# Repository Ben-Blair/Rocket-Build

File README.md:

# RocketSenior — canard-guided high power rocket

Senior capstone project: demonstrate closed-loop lateral guidance of a high power rocket
using forward canards, and handle the canard-wake-on-aft-fin interference problem
correctly.

This repository currently holds the **preliminary sizing tool**. It exists to answer the
questions you have to answer *before* you can draw anything in OpenRocket: how big is the
tube, how big are the fins, which motor, and can the canards actually do anything.

## Why a sizing tool instead of just using OpenRocket

OpenRocket is a verification tool. It answers "is *this specific* rocket stable, and how
high does it go." It cannot answer "what should my rocket be," because that depends on
constraints it knows nothing about:

- the internal diameter needed to house four canard servos (this sets your airframe size),
- the lateral acceleration you need for a visible manoeuvre,
- the static margin you are willing to trade away to get control authority,
- whether the canard wake reverses the sign of your roll moment.

This tool computes those, converges on a baseline, and then prints the numbers to type
into OpenRocket for an independent cross-check. Use both. Disagreement between them is
information.

## Quick start

```bash
pip install -r requirements.txt

python scripts/packaging_report.py   # what diameter do the actuators force on you?
python scripts/fetch_motors.py --diameter 54 --classes J K   # real thrust curves
python scripts/motor_trade.py        # rank every real L2 motor against the airframe
python scripts/sweep.py              # which (tube, motor, fin) combos meet requirements?
python scripts/baseline.py --plot    # full analysis + OpenRocket entry values
```

## Layout

```
out/
  RocketSenior.ork   GENERATED by scripts/make_ork.py -- do not hand-edit, see below
```

### The .ork is a build artifact, not the design

`out/RocketSenior.ork` is written from the same `DesignParams` the Python tool uses, and
`scripts/openrocket_check.py` regenerates it on every run. That is the point: the two
models cannot drift apart.

It also means **anything you change in the OpenRocket GUI and save back to that path is
destroyed the next time you run the check.** Open it to look, simulate, and cross-check
freely. If you want to tinker, `Save As` somewhere outside `out/` first. If a change is
worth keeping, it belongs in `design/configure.py` or `scripts/make_ork.py`, so that the
next regeneration carries it forward.

```
design/
  atmosphere.py   US Standard Atmosphere 1976, troposphere
  aero.py         Barrowman CNa & CP buildup, component drag buildup
  avionics.py     nav bay / nose packing, and the D7 flight computer trade
  bay.py          the printed canard bay: servo pockets, bearing seats, retainers
  configure.py    parameter set -> full vehicle -> requirement scoring, and the
                  frozen baseline airframe every script imports
  control.py      canard pitch authority, roll authority, wake interference, crossrange
  estimation.py   D8: observability per flight phase, attitude error budget, sensor specs
  flight_computer.py  the Stage 2 board: BOM, power budget, log budget, board envelope
  flutter.py      fin flutter margin
  geometry.py     nose / tube / fin set definitions, Barrowman CP geometry
  hinge.py        the hinge as a load path: shaft, bearing, coupling, root joint
  joints.py       all four tube joints -- a coupler costs bore, not length
  mass.py         geometric structural mass + editable subsystem budget, CG
  materials.py    material allowables, in one place
  motors.py       RASP .eng thrust curve parser + placeholder generic motors
  onshape.py      minimal Onshape REST API client
  onshape_build.py  emits Onshape Part Studio feature JSON
  packaging.py    actuator bay packaging + hinge moment + servo torque margin
  recovery.py     dual-deploy sizing, descent time, wind drift, soft-goods packing
  seal.py         the aft gas seal and the internal bulkhead, sized as pistons
  horizontal.py   horizontal-launch 3-DOF: fly the manoeuvre, then score the turn
  trajectory.py   3-DOF RK4 ascent to apogee
  tube_section.py airframe survival where holes are cut through it
  venting.py      static ports and bay vents: which volumes the altimeter may sense
scripts/
  agility_sweep.py      how agile can this airframe legally be, and what stops it
  avionics_report.py    nav bay + nose packing report and verdict
  avionics_trade.py     D7: the three flight computer architectures
  baseline.py           detailed baseline report + OpenRocket values
  bay_report.py         printed canard bay geometry and margins
  burn_time_study.py    why burn time is not a control-time knob
  canard_sweep.py       drives the CAD canards through +/-8 deg, checks clearances
  estimation_trade.py   D8: the four sensor sets, and what the estimate can know
  fetch_motors.py       download real .eng thrust curves from ThrustCurve.org
  hinge_report.py       hinge stack loads, fits and buildability
  horizontal_agility_sweep.py  the same search flown FLAT, where the answer changes
  make_*.py             build geometry in Onshape from the design modules
  motor_trade.py        rank every available L2 motor against the baseline airframe
  openrocket_check.py   automated cross-check against OpenRocket's engine
  packaging_report.py   diameter vs servo class table
  place_*.py            place built parts into Onshape Assembly 1
  recovery_study.py     descent, drift and the recovery footprint constraint
  robustness.py         Monte Carlo on static margin; sets the aft fin size
  flight_computer_report.py  the Stage 2 board's BOM, power, logging and envelope
  seal_report.py        the aft gas seal argument and check
  sil_demo.py           software-in-the-loop: closed-loop roll hold, bank-to-turn,
                        R12 failsafe -- synthetic sensors, no hardware
  sweep.py              design space sweep against requirements
  verify_cad.py         cross-check the design numbers against the Onshape model
  virtual_flight.py     3-D virtual flight: ballistic, skid-to-turn, bank-to-turn
docs/
  00-requirements.md    requirements, constraints, scoping, regulatory actions
  01-next-steps.md      ordered plan, the state of play, and 36 corrections
  02-motor-selection.md L2 motor trade study and decision
  03-openrocket-correlation.md  automated cross-check against OpenRocket's engine
  04-bill-of-materials.md       frozen parts list, masses and costs
  05-canard-module-build.md     CAD build sheet for the canard module
  06-avionics-selection.md      D7: the flight computer, and why it is staged
  07-state-estimation.md        D8: what the flight computer can know, and when
  11-agility-comparison.md      what this vehicle lacks versus a canard missile (VERTICAL)
  12-horizontal-agility.md      the same question flown flat -- 8.97 deg/s, and the
                                hinge bearing is what stops it. PROPOSAL, not frozen
  13-sil-demo.md                software-in-the-loop closed loop: how to run it, what
                                it proves, what it does not
  14-flight-computer-bom.md     the Stage 2 board, part by part: what to order, the
                                power and log budgets, and what was rejected
```

## How this fits with OpenRocket and RocketPy

Three tools, each for what it is actually good at. Do not try to make one do everything.

| Tool | Use it for | Do not use it for |
|---|---|---|
| **This repo** | Actuator packaging, control derivatives (`Cm_delta`, `Cl_delta`, `Cl_p`), canard/aft-fin wake interference, hinge moments, requirement-driven sizing sweeps across 100+ motors | Final apogee or drag numbers |
| **OpenRocket** | Validated stability and trajectory, Mach-dependent drag, dual-deploy and recovery sizing, fin flutter, the airframe truth a reviewer will trust | Anything involving a deflected control surface. It has no concept of one |
| **RocketPy** | 6-DOF flight with wind, Monte Carlo dispersion, and closed-loop control. `LinearGenericSurface` takes coefficient derivatives as functions of Mach, alpha, beta and body rates; `Controller` runs your control law at a fixed sampling rate against simulated IMU and barometer sensors | Preliminary sizing; it needs a vehicle before it can fly one |

The intended pipeline: size here → validate the passive airframe in OpenRocket → export
the derivatives from here into a RocketPy `LinearGenericSurface` → close the loop in 6-DOF
→ fly, and replace the interference factors with measured values.

## Model validity and what you must not trust

Read this before you quote any number from this tool in a report.

| Component | Status | Notes |
|---|---|---|
| Atmosphere | Solid | Standard model, valid to 11 km. |
| Barrowman CNa / CP | Good | Standard method. Valid subsonic, small alpha, attached flow. |
| Body lift (Galejs) | Approximate | Nonlinear term linearised about 4 deg alpha. |
| Drag buildup | ±20% at best | Component buildup with empirical form factors. Cross-check against OpenRocket, then against measured flight data. |
| Mass budget | Estimate | Every subsystem line is a guess until you weigh the part. Weigh things. |
| Trajectory | Good given the above | 3-DOF, no wind, perfect weathercocking. |
| Inertias | ±30% bulk, canard module measured | Crude analytical estimate for the airframe, with the canard module's CAD tensor superposed (`control.MEASURED_COMPONENTS`). Measure the rest before tuning gains. |
| Canard control derivatives | Approximate | Linear, quasi-steady, no wake effect on the canards themselves. |
| **Canard/aft-fin interference** | **Weakest part** | Empirical factors with no validation. Trends are believable, absolute values are not. Must be measured in flight. |
| Motor data | Real | 102 available 54 mm J/K certification curves from ThrustCurve.org in `data/motors/`. The `GENERIC` motors in `motors.py` are invented placeholders, kept only so the tool runs before a download. |

The interference model is the one to be honest about in your defense: it is a
physically-motivated parameterisation, not a validated prediction. The project plan
therefore makes measuring it a flight test objective rather than an assumption.

## Baseline result

75 mm (3 in) fiberglass airframe, 79.4 mm OD, 1361 mm long, 4 canards interdigitated 45°
from 4 aft fins, on a Cesaroni Pro54 J449 Blue Streak, actuated by four KST X08 Plus V6.0
servos on direct drive, with 100 g of nose ballast. 6.10 kg wet / 5.48 kg dry, apogee
1379 m (4525 ft), max Mach 0.531, static margin 2.03 cal at rail exit rising to 2.52 in
coast, 1.96 g of lateral authority at 8° of canard deflection, giving 424 m of crossrange
over an 11.4 second usable control window. Recovery is an 18 in drogue and 56 in main
deployed at 200 m, landing at 5.0 m/s after a ~0.93 km walk in a 15 mph wind.

Both fin sets were sized *together* by a Monte Carlo on margin robustness rather than
independently by nominal stability — canard semispan 0.85 cal, aft semispan 1.55 cal. They
pull in opposite directions, and searching them jointly under a probabilistic margin
constraint beats trading one against the other. See `docs/00-requirements.md` §7.

**The nose ballast is part of the design, not a contingency.** Real 9 g servos in place of
the 55 g budget placeholder removed ~180 g from ahead of the CG, which took P(SM < 1.0) to
1.8% against R1's 1% limit. 75 g of ballast is the minimum that satisfies R1; 100 g is the
design point and brings it to 0.6%. It is deliberately the last free parameter — a washer
stack you set after weighing the built vehicle, rather than fin area you commit to when you
cut the tube. See §7.1.

Every number above is an output of `scripts/baseline.py`. Regenerate them rather than
editing them by hand; they will move as the mass budget is replaced with weighed parts.

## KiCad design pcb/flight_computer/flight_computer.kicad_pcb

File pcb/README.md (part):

# `pcb/` — the Stage 2 flight computer board

One project so far: **`flight_computer/`**, the custom STM32F405 board that
`docs/06` selected, `docs/07` gave sensors to, and `docs/14` turned into a BOM. This
directory is where that BOM becomes a schematic and a board. **As of 2026-09-24 it is
placed, routed, DRC-clean and has a JLCPCB fab + assembly package** in
`flight_computer/fab/` — read `fab/ORDERING.md` and "What is not done" at the bottom before
you order: two parts are out of stock and every assembly rotation needs a look in JLC's
preview.

## Opening it

```
open pcb/flight_computer/flight_computer.kicad_pro
```

The schematics are still **KiCad 8 file format** (`.kicad_sch` 20231120) and open
unchanged in KiCad 8, 9 and 10. **`flight_computer.kicad_pcb` no longer is** — the
layout pass (below) is done with KiCad's own `pcbnew` Python module, which saves in
whatever format the KiCad it's running under uses, and on this machine that's
**KiCad 10.0.6, board format 20260206**. Opening the `.kicad_pcb` in KiCad 8 or 9 will
prompt to upgrade the file. If that matters, say so before more layout work happens
on it — reverting is easy now and gets harder every pass after.

The symbol and footprint bodies embedded in the files were copied from this
machine's libraries — so if a symbol looks odd in another KiCad install, that is the
first place to look.

`sym-lib-table` registers one project-local symbol library,
`RocketSenior.kicad_sym`, for the three parts that needed one (below).
`fp-lib-table` registers one project-local **footprint** library,
`RocketSenior.pretty`, holding exactly one footprint —
`MMC5983MA_LGA-16_3x3mm_P0.5mm`, redrawn for `U5`, for the reason in "MMC5983MA"
below. Both tables use `${KIPRJMOD}`, so there is nothing to install; everything
else is stock KiCad libraries.

### Verified state

Reproducible from a clean checkout by regenerating in order (see "How the board gets
built" below — running only some of these steps, or out of order, does not match this
table):

| check | result |
|---|---|
| `kicad-cli sch erc` | **0 errors, 0 warnings** |
| `kicad-cli pcb drc --severity-all` | **0 errors, 0 unconnected**; 14 warnings, all library-footprint cosmetics — listed under "Routing" |
| netlist vs. `scaffold/design.py` | **57 real nets, exact match** (96 in the raw KiCad netlist — the other 39 are its own one-per-pin `unconnected-(REF-Pad)` placeholders for every NC pin, not a discrepancy) |
| footprint assigned on every component | **76 / 76** |
| `python scripts/pcb_placement_report.py` | **1 failure** (`C3`, accepted), median 2.60 mm |

```
bash pcb/flight_computer/scaffold/regen.sh      # close KiCad first; it refuses otherwise
```

which is, in order: ERC, netlist export, `gen_pcb.py`, `layout.py`, `finish.py` (hand-drawn
critical copper + Freerouting + silkscreen), full-severity DRC, the placement report, and
`fab.py`. Freerouting is **not deterministic** — to rebuild *this* board rather than an
equally valid re-route, pass `--ses routing/board.ses` to `finish.py` (see its docstring).
It needs `tools/freerouting-2.4.1.jar` (64 MB, gitignored): download it from
<https://github.com/freerouting/freerouting/releases>. Java is already installed.

`kicad-cli` is not on `PATH` by default on this machine; it lives at
`/Applications/KiCad/KiCad.app/Contents/MacOS/kicad-cli`.

**Do not run `layout.py` twice in a row on the same file, and do not run it without
regenerating the skeleton first.** It loads whatever `flight_computer.kicad_pcb`
already contains and adds a full new set of passives/vias/zones on top; run on its
own prior output it silently doubles everything and every number above stops
matching. `gen_pcb.py` always rebuilds the board from scratch, so the correct order
is always: export the netlist, run `gen_pcb.py`, then run `layout.py` exactly once.

Before 2026-09-24 the 133 unconnected items were every signal net — the board was placed
and planed but not routed. They are all routed now; see "Routing".

Nothing here moved by exclusion — every DRC violation was fixed in geometry:

| | first pass | then | now | why |
|---|---|---|---|---|
| DRC violations | 23 | 11 | **0** | 12 were `U5`'s adjacent-pad clearance (fixed in copper, see "MMC5983MA"); the last 11 were GND stitching vias landing on `U2`'s pads — see "Planes" below |
| unconnected items | 136 | 133 | **133** | the 3 unstitched `GND` pads are stitched; the rest is unrouted signal |
| placement failures | — | 14 | **2** | the pre-routing placement pass — see "Placement" below |

## Placement — the pass before routing, and the check that holds it

**ERC and DRC are connectivity checks and cannot see geometry.** Both passed on a board
whose 12 pF crystal load cap sat **21.5 mm** from its crystal, with the 8 MHz oscillator
node routed the length of the MCU and past the IMU. `design/pcb_placement.py` is the check
that closes that gap, `scripts/pcb_placement_report.py` prints it, and `scripts/baseline.py`
carries the verdict so it cannot regress quietly. Read that module's docstring before
changing a limit — in particular, why the check is scoped to two-terminal passives plus
three named nets rather than run over every pad.

What moved, and the measured effect:

| | before | now |
|---|---|---|
| `OSC_IN` (crystal to MCU, worst pad) | 14.39 mm | **3.75 mm** |
| `OSC_OUT` | 5.98 mm | **4.96 mm** |
| `GNSS_RF` (`U8` pin 11 to the u.FL) | 13.93 mm | **2.59 mm** |
| `C2`, 100 µF bulk, to the star point | 11.21 mm | **4.60 mm** |
| `R1`/`C4`, the regulator's enable and bypass | 14.3 / 13.6 mm | **2.99 / 1.98 mm** |
| median over all checked pads | 3.47 mm | **2.59 mm** |
| failures | 14 | **2** |

The moves that made room, all in `scaffold/gen_pcb.py`'s `PLACE`:

- **`J10` and `SW1` were in the two best pockets on the board** and are bring-up-only
  parts. `J10` (debug UART) held a 3.5 × 11.2 mm channel beside `U1` — which is *why*
  `C2`/`C4`/`R1` had been hand-relocated 14 mm away in an earlier pass, with a note saying
  the corner was saturated. It was saturated by a debug header. `SW1` sat in the only pocket
  that could take the crystal. Both are grouped with `J3` on the aft edge now; `NRST` is on
  the SWD header anyway, so `SW1` belongs there electrically as well as ergonomically.
- **`TP3` (a GND probe point) had claimed the gap between `U1` and its VIN cluster.** A test
  point's courtyard is 1.25 × 0.00 mm, so it slips into gaps no real part can claim.
- **`J5` moved to the forward edge** beside `U8`'s RF pad, which points at the nose where
  the antenna is. `U8` shifted 2.0 mm aft to open the strip — its courtyard is 11.8 mm wide
  against a 9.7 × 10.1 mm package and left only 3.0 mm of edge for a 4.4 mm connector.
- **`Y1` moved against `U2` pins 5/6, at 180°** so its `OSC_IN` pad faces the MCU and the two
  traces do not cross.

**`U5` did not move, and is confirmed not to have moved**: pad 1 is still at
(162.7500, 109.2250) — `pcb_placement.self_check()` asserts it on every run, because a
pad-rotation sign error would otherwise be invisible in the aggregate.

### The two remaining failures, both accepted

`C3.1` at **3.40 mm** and `R1.1` at **2.99 mm** against a 2.5 mm `VIN` limit. The aft-left
corner really is saturated once the four servo headers, the pack connector, the regulator,
the inductor and the power LED are in it — that part of the earlier note was right. Both are
about 1 mm over a limit set by judgement rather than by a datasheet. If the buck's input loop
ever needs to be tighter than this, the lever is `docs/14`'s own rule — *"if layout wants
more, take it out of height, not width"* — not another shuffle of the same corner.

## How the schematic is drawn, and why it looks like that

Four hierarchical sheets — `power`, `mcu`, `sensors`, `io` — under a root sheet that
carries the board-level notes.

**There are no drawn buses.** Every pin gets a short stub with a global label or a
power symbol on the end. That is a deliberate trade: it makes the netlist exactly
what `design.py` says and nothing else, and it means the auto-placement of symbols on
the sheet carries no meaning at all. **Rearranging the sheets into something a human
would draw is expected work, and it cannot break connectivity** as long as you move
labels with their pins. Sheet sizes were picked as the smallest ISO size each fit on
(io A3, power/sensors A2, mcu A1).

## Bus map — this is `docs/14`, unchanged

```
SPI1  CS1_IMU     PA4    ICM-42688-P    alone on the bus, 1 kHz burst on DMA
SPI2  CS2_MAG     PB12   MMC5983MA      100 Hz
      CS3_BARO    PC7    MS5611         50 Hz
SPI3  CS4_FLASH   PB5    W25Q128JV      log flash, write-mostly
USART1 PA9/PA10          MAX-M10S       10 Hz UBX
USART2 PA2/PA3           debug console  bring-up only
TIM4  CH1-4  PB6 PB7 PB8 PB9            4x servo PWM, 333 Hz / 1520 us
SWD   PA13 PA14 (+ PB3 SWO)
USB   PA11/PA12 full speed, 8 MHz HSE crystal
```

CS net names are `CS1_IMU`, `CS2_MAG`, `CS3_BARO`, `CS4_FLASH` so both `docs/14`'s
number and the function are in the name.

**Flash only — no microSD**, per `docs/14`'s socket-eject argument. The SDIO pins
(PC8-PC12/PD2) are not all free because SPI3 took PC10-PC12; if a microSD is ever
wanted, that is the trade to reopen.

**No pyro, no continuity, no e-match anything.** An independent StratoLoggerCF fires
the charges. This is `docs/14`'s non-negotiable and the board honours it.

## Things found while drawing it

These came out of reading datasheets to place pins, and several of them change a part,
a component count or a footprint. **None of them touches ±4000 or the airframe
freeze.**

### 1. `docs/14` names the wrong regulator — TPS62163 is 5.0 V, not 3.3 V

`docs/14`'s BOM row reads `3.3 V regulator | TPS62163DSGT`. TI's own device-options
table (SLVSAM2E, *TPS62160/61/62/63*, §5 Device Voltage Options) maps the suffixes:

| output | part |
|---|---|
| adjustable | TPS62160 |
| 1.8 V | TPS62161 |
| **3.3 V** | **TPS62162** |
| 5.0 V | TPS62163 |

**The 3.3 V part is TPS62162DSGT.** Verified against TI's own PDF, not a mirror:
`ti.com/lit/ds/symlink/tps62162.pdf`, SLVSAM2E §5 *Device Voltage Options*, which also
confirms DSG = WSON(8) and the DSG pinout the power sheet is wired to (1 PGND, 2 VIN,
3 EN, 4 FB, 5 AGND, 6 VOS, 7 SW, 8 PG).

**This is now fixed in all three places** — the schematic already had it, and
`docs/14-flight-computer-bom.md` and `design/flight_computer.py` have been changed from
`TPS62163DSGT` to `TPS62162DSGT`. `out/flight_computer.txt` was regenerated
(`python scripts/flight_computer_report.py --write`) so the report no longer copies the
wrong line. The intent in `docs/14` was never ambiguous ("3.3 V regulator", 2S in,
112 mA logic rail) — it was a wrong MPN, and ordering the line as written would have put
5.0 V onto the 3.3 V logic rail.

Wired per the same datasheet: `FB` (pin 5) to AGND, which is what TI specifies for
the fixed-output versions; `VOS` (pin 6) is the output sense and goes to the 3.3 V
rail; `PG` is open-drain and gets a 100 k pull-up, landed on PC13 so firmware can see
the rail come up.

### 2. The magnetometer needs a 10 µF capacitor that was in nobody's parts count

MMC5983MA **pin 10 is `CAP`** — "Connect a 10 µF capacitor for SET/RESET" (MEMSIC
MMC5983MA Rev A, Pin Description). That is not decoupling; it is the reservoir that
drives the degauss coil, and the SET/RESET cycle is exactly what this vehicle needs
the magnetometer for (`docs/12`, roll observability). It is `C23` on the sensors sheet.

Full pin list taken from that table, since no stock KiCad symbol exists:
`1 SCL/SPI_SCK, 2 VDD, 3 NC, 4 SPI_CS, 5 SPI_SDO, 6-8 NC, 9 GND, 10 CAP, 11 GND,
12 NC, 13 VDDIO, 14 NC, 15 INT, 16 SDA/SPI_SDI`.

### 3. The MS5611 has *two* CSB pins, and the stock KiCad symbol is right

`Sensor_Pressure:MS5611-01BA` puts `CSB` on both pin 4 and pin 5, which looks like a
library bug. It is not. The TE datasheet's PIN CONFIGURATION table has a merged cell
spanning pins 4 and 5 — "Chip select (active low), **internal connection**". Both
pads go to `CS3_BARO`. Left as-is, this is the kind of thing that gets "fixed" during
layout and quietly breaks the part.

## Pinouts, and how much to trust each one

| part | pinout source | confidence |
|---|---|---|
| STM32F405RGT6 | stock `MCU_ST_STM32F4` symbol | high |
| MS5611-01BA03 | **TE datasheet read directly** (pin table above) | high |
| MMC5983MA | **MEMSIC Rev A read directly** — pinout *and* land pattern, and the footprint is now redrawn from it | high |
| W25Q128JVS, MAX-M10S, USBLC6 | stock KiCad symbols | high |
| TPS62162DSGT | **TI SLVSAM2E read directly** | high |
| **ICM-42688-P** | **TDK DS-000347 rev 1.6 read directly** | high |

## Datasheet verification — the pinouts are no longer single-sourced

An earlier revision of this file said DS-000347 could not be fetched and that the
ICM-42688-P pinout rested on one SnapEDA-derived symbol. **That has been closed.** The
403 was not a paywall or a bot wall on the file — it was a missing browser
`User-Agent`/`Referer`. This gets the real PDF:

```
curl -L -o ds347.pdf \
  -H "User-Agent: Mozilla/5.0 (Macintosh; Intel Mac OS X 10_15_7) \
AppleWebKit/537.36 (KHTML, like Gecko) Chrome/140.0.0.0 Safari/537.36" \
  -H "Referer: https://product.tdk.com/" \
  https://product.tdk.com/system/files/dam/doc/product/sensor/mortion-inertial/\
imu/data_sheet/ds-000347-icm-42688-p-v1.6.pdf
```

The same trick (UA + a `Referer` on the vendor's own domain) worked for MEMSIC and TI.
Do not re-record any of these as "unfetchable".

| document | what was read | SHA-256 of the PDF |
|---|---|---|
| TDK InvenSense **DS-000347 rev 1.6**, 110 pp | §4.1 Table 10 *Signal Descriptions*, Fig. 5 pin-out, §10.2 package drawing | `5710af93…2ce1b9c` |
| MEMSIC **MMC5983MA Rev A**, 20 pp (4/3/2019) | Pin Description table, p.11 SPI connection, p.20 package drawing + LAND PATTERN | `d82083b9…5731f7` |
| TI **SLVSAM2E** (TPS62160/61/62/63) | §5 Device Voltage Options, §6 DSG pin configuration | — |
| u-blox **UBX-20035208 R08**, 24 pp (30-Jan-2026) | §3.1 Table 10 *Pin assignment*, §4.2 Table 13 *Operating conditions* | `e36d9c85…8df6bec` |

**`U8`'s whole pin map was checked against Table 10 and is correct as drawn — including
every no-connect.** Pin 15 `VIO_SEL` is the one worth naming: *"Connect to GND for 1.8 V
supply, or leave open for 3.3 V supply."* **Open is the 3.3 V setting and is deliberate**;
tying it to GND would drop `V_IO` to 1.8 V and break every interface on the board. Pins 13
and 14 (`LNA_EN`, `VCC_RF`) are outputs, open because the antenna is passive (`docs/14`).
Pin 6 is `V_BCKP` and sits on `+3V3`, i.e. the same rail as `VCC`, so the backup domain dies
with the board and **every power-up is a cold start** — accepted, not missed: `docs/14`
budgets 60 minutes armed on the pad, which is many times a cold TTFF.

### ICM-42688-P pin table, from DS-000347 §4.1 Table 10 verbatim

| pin | name | datasheet says | schematic does |
|---|---|---|---|
| 1 | AP_SDO / AP_AD0 | SPI serial data out (4-wire) | `SPI1_MISO` |
| 2 | RESV | *No Connect or Connect to GND* | NC |
| 3 | RESV | *No Connect or Connect to GND* | NC |
| 4 | INT1 / INT | interrupt 1 | `IMU_INT1` |
| 5 | VDDIO | IO supply | `+3V3` |
| 6 | **GND** | power supply ground | `GND` |
| 7 | **RESV** | **"Connect to GND"** — not optional | **`GND`** |
| 8 | **VDD** | power supply voltage | `+3V3` |
| 9 | INT2 / FSYNC / CLKIN | see the FSYNC note below | NC |
| 10 | RESV | *No Connect or Connect to GND* | NC |
| 11 | RESV | *No Connect or Connect to GND* | NC |
| 12 | AP_CS | SPI chip select | `CS1_IMU` |
| 13 | AP_SCL / AP_SCLK | SPI serial clock | `SPI1_SCK` |
| 14 | AP_SDA / AP_SDIO / AP_SDI | SPI serial data in (4-wire) | `SPI1_MOSI` |

**Pins 6 and 8 were the ones worth checking, and the SnapEDA symbol had them right:
6 is GND, 8 is VDD.** The whole symbol matched, pin for pin. The old warning about
VDD/GND swapped on a 2.5 × 3.0 mm LGA can be retired.

**What did change: pin 7.** The datasheet distinguishes the reserved pins, and it is
the only one of the five that reads *"Connect to GND"* flat, with no "No Connect or"
in front of it. It was a no-connect here — the conservative-looking choice that was
in fact the wrong one. It is now on `GND` in `scaffold/design.py`, the schematic and
the board. Pins 2, 3, 10 and 11 genuinely are "No Connect **or** Connect to GND", so
leaving them NC is compliant and they stay NC.

**FSYNC (pin 9) is safe as a no-connect, but only because of a register default.**
`INTF_CONFIG5` (bank 1, 0x7B) bit 2:1 `PIN9_FUNCTION` resets to `00` = INT2, which is
an *output*, so a floating pin 9 drives nothing and floats nothing. The datasheet's
"Connect to GND if FSYNC not used" applies to the FSYNC configuration only. **This is
now a firmware constraint: do not set `PIN9_FUNCTION` to `01` (FSYNC) on this board.**
There is no pad to ground it from if you do. Note `FSYNC_CONFIG` (0x62) resets to
`0x10`, i.e. FSYNC tagging into `TEMP_OUT` LSB is *already enabled* — harmless while
pin 9 is INT2, not harmless if you switch the pin.

### Footprints, against the two land patterns

**ICM-42688-P — `Package_LGA:LGA-14_3x2.5mm_P0.5mm_LayoutBorder3x4y` is correct, no
change.** DS-000347 §10.2 gives the package, and the KiCad footprint reproduces it
exactly: pad centres at **±1.1625 mm** on the 4-pin columns and **±0.9125 mm** on the
3-pin rows — the same two numbers the drawing dimensions as `2X 1.1625` and
`2X 0.9125`. Body 3.0 (E) × 2.5 (D) mm, 0.5 pitch, 4+3+4+3 with pin 1 top-left in top
view and counter-clockwise numbering. Pads are 0.625 × 0.35 mm against a 0.475 × 0.25
terminal (`L` × `W`), i.e. a normal IPC expansion. The library entry is labelled for
an ST LSM6DS3TR-C, which is why it needed checking; the geometry is the same package
and it lands.

**MMC5983MA — the assigned footprint was wrong, and it has been changed.** It was
`Package_LGA:LGA-16_3x3mm_P0.5mm_LayoutBorder3x5y`, which is **5 pads on two sides and
3 on the other two**. The MMC5983MA is **4 pads on every side** (MEMSIC Rev A p.20,
top view: 4/3/2/1 across the top, 5-8 down the left, 9-12 across the bottom, 16/15/14/13
down the right). Nothing but the pitch would have matched. That part would not have
soldered.

It is now **`RocketSenior:MMC5983MA_LGA-16_3x3mm_P0.5mm`**, a project-local
footprint in `RocketSenior.pretty` drawn for this part, and it matches the MEMSIC
LAND PATTERN drawing exactly:

| | MEMSIC Rev A p.20 | `RocketSenior:MMC5983MA_LGA-16_3x3mm_P0.5mm` |
|---|---|---|
| pads per side | 4 | 4 |
| pitch | 0.500 | 0.5 |
| pad size | 0.450 × 0.300 | 0.45 × 0.30 (rot 90 on the side columns) |
| row-to-row, centre to centre | 2.550 both axes | ±1.275 both axes |
| pad 1 | right end of the top row | right end of the top row |

(The 2.550 dimensions are centre-to-centre, not outer-edge — the extension lines land
on the pad midlines. Checked by magnifying the drawing; it is the one reading that
makes the numbers close.)

#### Why it is project-local, and why `U5` is at 0° and not 270°

The copper above is the same copper the stock `Package_LGA:LGA-16_3x3mm_P0.5mm`
has — that library entry is fine, and it is where this geometry was copied from.
The difference is **numbering**. Both number counter-clockwise, 4 per side, so pin
*n* lands on pad *n* for all 16; what differs is where the sequence starts. The
stock footprint's pad 1 is the top of the **left column**, while the chip's pin 1 is
the right end of the **top row** — one 90° step apart (stock pad *n* sits where chip
pin *n+4* would). Left at 0° on the stock footprint, the die sits rotated 90° CCW off
datasheet-upright and mag X/Y come out swapped against the board.

**For one revision that was corrected by placing `U5` at 270°. The axis answer was
right and the copper was wrong.** KiCad stores each pad's rotation **absolutely** in
the board file, not relative to its footprint: rotating the footprint 270° subtracts
270° from every pad's effective local angle. The side pads lose the 90° that made a
0.45 × 0.30 rectangle fit a 0.5 mm pitch, the 0.45 mm dimension ends up running
*along* the pitch, and adjacent-pad gaps collapse from 0.200 mm to **0.05 mm** —
under the `Default`/`Power` netclass's 0.127 mm and under JLCPCB's 0.127 mm minimum.
That produced 12 DRC clearance violations. They were never excluded; the geometry
was fixed.

The fix moves the 90° step out of the *placement* and into the *footprint*: the
local copy carries the same land pattern with the **chip's own numbering**, so `U5`
is placed at **0°**, upright, and nothing is rotated. Consequences:

- **Copper is the land pattern again.** All 16 adjacent pairs measure **0.200 mm**
  edge-to-edge (0.5 pitch − 0.30 pad) on the four sides, and 0.212 mm across each
  corner. Measured from `pcbnew`'s real pad polygons, not from size arithmetic — a
  pad with a wrong rotation flag cannot hide from that check. The 12 clearance
  violations are gone from `kicad-cli pcb drc`.
- **The die is datasheet-upright, and the axis convention `docs/12` needs is
  unchanged.** Mag axes aligned with board, mounting matrix board-in-airframe only.
  The strongest evidence that nothing moved: **every one of the 16 pad centres, and
  every net on them, is bit-identical to the old 270° placement.** Pad 1 is still at
  (162.7500, 109.2250). Only the pad rectangles' orientation changed. `docs/12` leans
  on this part for roll observability, so this was worth confirming rather than
  assuming.
- **`PLACE["U5"]` in `scaffold/gen_pcb.py` is `0` now**, `scaffold/design.py` and
  `scaffold/gen.py` both name the local footprint, and `gen.py` writes the
  `fp-lib-table` that resolves it — so a regen cannot revert any of it. `ksym.py`
  searches `RocketSenior.pretty` before the stock library, so a project-local redraw
  always wins over a same-named stock part.
- **Pin 1 is marked three ways, all at the top-right corner**: the silkscreen arrow
  above pad 1, the `F.Fab` outline chamfer, and a deliberately oversized filled
  circle on `F.Fab` at (1.9, −1.9). That circle used to be welded on at generation
  time by `gen_pcb.py`'s `EXTRA_FAB_MARK`, because the part was rotated on a
  footprint labelled for its sibling; it is now **drawn into the footprint itself**,
  so it is right in the footprint editor and on any other board too. Do not re-add a
  `U5` entry to `EXTRA_FAB_MARK` — that would draw the dot twice.

KiCad's own `--schematic-parity` check resolves the local library and reports **no
issue at all for `U5`** — the board's embedded copy of the footprint matches the
library exactly.

### Residual risk

- **Solder-paste apertures are the library's, not the vendor's.** Neither vendor
  publishes a stencil recommendation; both footprints use KiCad's default 1:1 paste
  layer. For two bottom-terminated 0.5 mm-pitch parts that is normal practice, not a
  verified number.
- **No 3D models were checked**, so nothing has confirmed that the ICM's pin-1 corner
  chamfer or the MMC's package outline agree with the footprint's fab layer. The
  local MMC footprint keeps the stock `LGA-16_3x3mm_P0.5mm.step` reference — the
  package body is the same, but **the model was drawn for the stock numbering**, so
  if it carries a pin-1 feature of its own it will point at the top of the left
  column, not the top-right corner where this footprint's pin 1 is. Believe the
  `F.Fab` marks, not the render.
- **The MMC5983MA's `MAG_CAP` net is not really a separate node.** MEMSIC Rev A p.11:
  "VDD and CAP pins are shorted together inside the device." `C23` (10 µF) therefore
  sits on the same node as `+3V3` through the package. That is exactly what MEMSIC's
  own SPI connection diagram draws, so it is kept as drawn — but **do not route
  `MAG_CAP` as a signal**, and do not let anyone "clean it up" by merging it into
  `+3V3` on the schematic, which would move the 10 µF away from the CAP pad.
- **DS-000347 rev 1.6 is not the newest revision** — TDK is at least at 1.9. Nothing
  read here (pin table, package drawing, `PIN9_FUNCTION`, `FSYNC_CONFIG`) is the kind
  of thing that moves between revisions, but the ordering check before fab should be
  done against whatever revision is current then.
- **The ICM footprint's toe extends to 1.475 mm against a 1.5 mm package half-width**,
  i.e. the land sits entirely under the body with no external fillet. That is inherent
  to LGA and matches the drawing; it just means optical inspection cannot see these
  joints and X-ray is the only real check.

## Power, and the rail split `docs/14` asked for

`docs/14`: the KST X08 runs straight off the 2S pack, so there is no BEC, and
"separate supply from the IMU" becomes a separate feed and filter off a star point at
the pack. On the board that is:

- **`VBATT`** — raw 2S from `J1`, **two wire pads for an 18 AWG XT30 pigtail** (was a
  JST-GH rated 1 A per contact — see "Routing and fab"). Goes to the four servo headers `J6`-`J9`
  and nowhere else. Its own netclass (`ServoPower`, 1.2 mm tracks, 0.3 mm clearance)
  because it carries the **4.1 A all-four-stalled** case from `docs/14`.
- **`VIN`** — the logic branch, through ferrite `FB1`. Making it a separate net is
  what puts the star point in the netlist instead of in a comment.
- **`+3V3`** — 1 A buck. The 112 mA logic rail has plenty of headroom.
- **`VDDA`** — through `FB2` off `+3V3`, with 1 µF ‖ 10 nF.

Each servo header is a normal 3-pin SIG/V+/GND so a servo lead plugs straight in.
**Nothing on this board feeds a servo from 3.3 V** — check that first if you rearrange
the power sheet.

`J4` is USB-C, and **VBUS is not connected to any rail**: the board is powered from
the pack. `D1` + solder jumper `JP1` (**default open**) exist so you can close the
link and run the board off USB on the bench without a pack. Do not close it with a
pack plugged in.

## Board

70.0 × 45.0 mm outline on `Edge.Cuts`, 4 layers, 1.6 mm, ENIG, four M2.5 corner
holes. Against `docs/08`'s sled that leaves +39.0 mm long / +14.4 mm wide / +9.1 mm
tall. **`docs/14`: hold 70 × 45; if layout wants more, take it out of height, not
width** — the board is the one line in the nav bay whose size is a design decision.

Major parts sit at `docs/14`'s zoning; passives are placed next to the pin they
decouple:

- **aft/left** — pack in, regulator, four servo headers. The noisy end.
- **centre** — MCU, with the IMU below it over the solid ground pour.
- **forward/right** — magnetometer `U5` and the GNSS receiver, diagonally as far from
  the servo headers and the battery lead as a 70 × 45 outline allows.

That last one is a requirement, not aesthetics:
`estimation.required_magnetic_cleanliness()` gives **18.0 mgauss** against
**40 mgauss** from a single untwisted 1 A servo lead at 50 mm. Twisted pairs on the
servo leads and keeping the 2S run off the forward end are how that budget gets met.

Netclasses are in the `.kicad_pro`, mirrored by `NETCLASS_PATTERNS`/`TRACK_WIDTH` in
`scaffold/layout.py`: `Default` and `Power` at 0.127 mm clearance (anything wider fails
against the LQFP-64 and LGA pad pitches), `ServoPower` at 0.3 mm / 1.2 mm tracks, `USB` with
a 0.2 mm / 0.4 mm differential pair, and **`RF` at 0.36 mm for `GNSS_RF`**.

**0.36 mm is 50 ohm on this stackup**, and 50 ohm is what the part asks for: MAX-M10S `RF_IN`
has `Zin` = 50 ohm with a built-in DC block (u-blox UBX-20035208 R08, Table 13). Hammerstad
microstrip over `In1` — h = 0.2104 mm, er = 4.5, t = 35 um — gives **59.9 ohm at the
`Default` 0.25 mm** and 50.0 ohm at 0.360 mm. `GNSS_RF` had been sitting in `Default`, i.e. a
~20% impedance error on the one net on this board that has an impedance.
`scripts/pcb_placement_report.py` prints the solve rather than leaving 0.36 as a constant.

### One routing rule that is not a netclass: the `VBATT` trunk

`ServoPower` is a single width, but `VBATT` carries two very different currents. The branches
to `J6`-`J9` take **<= 1 A each** and 1.2 mm is right for them (and is what fits a 2.54 mm
header). The trunk from `J1` to the branch point carries `docs/14`'s **4.1 A all-four-stalled**
case, which that document explicitly calls "a conductor question".

On 1 oz external copper, 1.2 mm is **2.73 A** at a 10 degC rise; at 4.1 A it runs about
**27 degC** hot. 2.0 mm brings that to ~11 degC. **Route the `J1` -> branch-point trunk at
2.0 mm**, keep the branches at 1.2 mm, and keep the whole run tight over `In1` (see "Planes").
It is a short run through an otherwise empty corner, so this costs nothing — but it has to be
done by hand, because a netclass cannot express "this part of this net".

## How the board gets built — two separate, one-way passes

`flight_computer.kicad_pcb` is not hand-edited directly and is not one script's
output; it comes from two passes that must run **in order**, and each one **destroys
what the other one did if run out of order or twice**:

1. **`scaffold/gen_pcb.py`** — rebuilds the *entire* board from KiCad's own exported
   netlist: layers, stackup, nets, every footprint at its `PLACE[...]` position (or
   parked off-board if not in `PLACE`), the outline and its notes. This is the
   skeleton generator described lower down; it has no memory of anything a previous
   layout pass did. Run it after any schematic/`design.py` change, before touching
   layout.
2. **`scaffold/layout.py`** — the hand-layout pass, run once against that skeleton
   with KiCad's own bundled Python (it needs the real `pcbnew` module, which is not
   on a normal `python3`):
   ```
   /Applications/KiCad/KiCad.app/Contents/Frameworks/Python.framework/Versions/3.9/bin/python3 \
     pcb/flight_computer/scaffold/layout.py pcb/flight_computer/flight_computer.kicad_pcb
   ```
   It places every passive next to the pin it decouples (anchored by shared net,
   nearest IC preferred over a connector, with a small hand-curated override table
   for rail/bulk caps that a shared `+3V3`/`VBATT`/`GND` net can't disambiguate on
   its own — see `OVERRIDE_ANCHOR` in the script), pours and fills the ground planes,
   stitches every surface-mount `GND` pad into them with its own via, adds the one
   hand-drawn stitch in `MANUAL_GND_STITCH` (`U1`'s exposed pad — see "Planes"), and
   stops. **It does not route signal nets** — see below.

Running `layout.py` a second time on its own output does not "improve" the layout —
it loads whatever is already in the file and adds a whole second set of
passives/vias/zones on top, silently doubling everything. If you need to change
something after `layout.py` has run, either edit the `.kicad_pcb` directly in KiCad,
or start over from step 1.

### Placement

All 53 passives that `gen_pcb.py` parks off-board are placed by `layout.py`, each
next to the specific pin it serves (not just "somewhere on the net" — see
`resolve_anchors` / `OVERRIDE_ANCHOR`). Collision is resolved against real `F.CrtYd`
courtyard geometry read from `pcbnew` (not a pad-bounding-box guess, which
undercounts a JST connector's or a switch's real body badly), by the same kind of
push-apart relaxation `gen_pcb.py` already used for the major parts. Four items
needed a hand nudge afterward into open space nearby, each individually checked
against `kicad-cli pcb drc` before being hard-coded — see `MANUAL_FIXUP` in the
script; the comments there say why each one didn't fit where the automatic pass put
it. The aft/left corner (four servo headers + `J1` + the regulator + `J10`, all
`docs/14` zoning decisions, not this pass's to move) is genuinely saturated — there
was no pocket left near `J1` itself for its own bulk caps, which live one zone over
instead.

### Planes

`In1.Cu` and `In2.Cu` are each one solid `GND` pour, the whole board.

**`In2` used to be split in two** at `x = 120.5`, with a 1.5 mm copper gap, so that "servo
return current has no direct path across `In2` under the sensors". **That never worked and
could not have**: both halves were net `GND` and `In1` is an unbroken full-board pour, so
every stitching via tied them together. They were one node the whole time.

What the gap did do was real. The stackup is `F.Cu` / 0.2104 prepreg / `In1` / 1.065 core /
`In2` / 0.2104 prepreg / `B.Cu`, so a `B.Cu` trace references `In2` at 0.21 mm while `In1`
is 1.28 mm away. **Any `B.Cu` trace crossing `x = 120.5` lost its return path** — and
`SERVO1-4`, `+3V3` and `VIN` all have to cross it, because the MCU is at `x = 137` and the
regulator and servo headers are at `x = 103.5-117`. The split was costing exactly the thing
it was meant to protect, on the layer where the routing has to happen.

**Servo-return isolation comes from routing, not from a slot**: keep the `VBATT` trunk tight
over `In1` so its return image stays directly underneath it. At 0.21 mm of prepreg that image
is a ~0.1 mgauss dipole at the magnetometer against the 18.0 mgauss budget — four orders of
margin, which is why the binding magnetic risk in that budget is the untwisted servo *leads*
off-board and never the on-board copper. A genuine split would have to slot `In1` as well and
enforce a single star point, and it would put a plane slot under a board carrying both an IMU
and a magnetometer. That is a decision, not a default.

Every `GND` pad gets its own short stub and via down into `In1`. The escape direction is
searched over eight directions at five increasing offsets, and the first position clearing
**0.40 mm** to the nearest other-net pad *bounding box* is taken; if none clears, the best
available is used and the script **says so** on stdout.

That replaced a best-of-four-cardinal-directions-at-one-offset search measured **centre to
centre**, which is what produced all 11 of the previous pass's DRC violations: centre-to-centre
treats a 1.7 mm LQFP-64 finger and an 0402 terminal as the same point, so an escape "1.4 mm
from the centre" of a long pad was landing 0.10 mm off its edge. On a 0.5 mm-pitch part the
cardinal directions all run down a row of pins and the diagonals are the only way out.

**The three `GND` pads that used to be left out are stitched. There are no `GND`
items in `kicad-cli pcb drc`'s unconnected list at all now.** What they actually
were is worth recording, because an earlier revision of this file diagnosed two of
them wrongly:

- **`SW1` pin 2 and `J5` pin 2 — the zone filler was innocent.** This file used to
  say the filler was pruning the copper around their vias as an "island". It was
  not: those vias sit inside solid `In1` pour, checked against the filled polygons
  with holes accounted for. The real cause is **duplicate pad numbers**. `SW1`
  (`SW_SPST_TL3342`, a 4-terminal tactile switch) has *two* pads numbered `2`, and
  `J5` (U.FL) has two as well — one netlist pin, two separate lumps of copper.
  `stitch_gnd_vias` walked the netlist and took `next(p for p in fp.Pads() if
  p.GetNumber() == pin)`, i.e. **the first pad only**, so the second lump of each
  pair never got a stub and never touched the plane. The loop now stitches *every*
  pad carrying the number. It also skips through-hole pads, which reach `In1`
  through their own barrels and need no escape via — that is what keeps `J4`'s four
  same-numbered USB-C shield tabs from collecting four redundant vias, and it is why
  the stitched-via count reads 65 rather than 69 while *more* copper is connected.
- **`U1`'s WSON-8 exposed pad (pin 9)** is real and is handled by hand. It sits
  exactly at the footprint's own centre on a 2×2 mm body with pins 6/7 straddling
  it, so no cardinal escape direction clears them, and a via dropped into the pad
  itself would be an unplugged 0.3 mm drill under a bottom-terminated part — a
  solder-wicking risk taken for nothing, since the TPS62162 dissipates on the order
  of **40 mW** here (112 mA at 3.3 V, ~90 % efficient) and needs no thermal path at
  all. `MANUAL_GND_STITCH` in `scaffold/layout.py` runs a 0.25 mm `F.Cu` track east
  out of the pad at *y* = 139.25 to pin 5 (`GND`), which already has its own stub and
  via. The only other-net copper it passes is pin 6 (`+3V3`), and the measured gap
  is **0.250 mm** against the 0.127 mm `Power` requirement. If a proper thermal via
  array under the EP is ever wanted, it is a fab-time decision about plugged vias,
  not a connectivity one.

### Routing and fab (2026-09-24) — `scaffold/finish.py` and `scaffold/fab.py`

`layout.py`'s greedy router (`route_signal_nets`) is still off, for the reason it always
was: two-bend Manhattan paths cannot route an LQFP-64 escape on a populated board, and it
fell back to shorts. The board is routed by a **third pass, `scaffold/finish.py`**, run
exactly once on `layout.py`'s output:

1. **Inner layers typed as power planes.** `In1`/`In2` were "signal" layers; left that way
   Freerouting routes through the GND pours and the zone filler cuts the plane round each
   track.
2. **Copper a netclass cannot express, drawn by hand and locked** (Freerouting routes
   around locked copper):
   - **`VBATT` at 2.0 mm, the whole run.** `J6`-`J9` pin 2 all sit at *x* = 106.04 between
     pin 1 (signal) and pin 3 (GND); a 2.0 mm spine straight down that column clears both
     by 0.69 mm against the 0.3 mm `ServoPower` clearance, so every header hangs off one
     2.0 mm conductor and there is no narrower "branch" — the J9→J8 segment carries three
     servos anyway. `C1` moves 1.2 mm and flips so its `VBATT` pad sits *on* the trunk's
     corner instead of in its way.
   - **`GNSS_RF`**: `U8` pin 11 straight to `J5` at 0.36 mm, 2.59 mm long.
   - **`U1` pins 2/3 (`VIN`, `EN`)**: left to the autorouter, `VIN` boxed `R1`'s `EN` pad in
     (the one unrouted link of the first run). `R1` turns 180° and both leave between
     `U1`'s two GND stitch vias as parallel 0.2 mm tracks (0.15 mm clear of each via).
   - **`J4` pins A1/B12 (GND)** are tied on F.Cu to the USB-C shield tab. `layout.py`'s
     stitch via there ended up on an island of `In1`/`In2` once the router's vias
     surrounded it (DRC: "via connected on one layer").
3. **Freerouting 2.4.1**, headless, via Specctra DSN/SES with KiCad's own
   `ExportSpecctraDSN`/`ImportSpecctraSES`. It completes every signal net.
4. **Silkscreen**: every reference re-placed at JLCPCB's 1.0 mm minimum where it overlaps
   no pad, via, other label, other part's silk or other part's *body* (a label under a
   part vanishes on assembly — the first pass put "J10" under the GNSS module). Eight
   0402s in the MCU cluster have no such spot; their silk reference is hidden and they
   are on the assembly drawing (`fab/flight_computer-assembly.pdf`). "+"/"−" marks sit
   beside the `J1` wire pads.

**The 14 DRC warnings that remain are all library-footprint cosmetics, and none is
excluded** (there are still no exclusions in this project): 8 × `lib_footprint_mismatch`
(the embedded copies of stock footprints are older than KiCad 10.0.6's library — no pad
changed), 4 × `silk_over_copper` on `SW1` (the stock TL3342 footprint's own silk crosses
its pads; the plotter clips it), 2 × `silk_edge_clearance` on `J4` (its outline runs to the
edge because the connector is edge-mounted — below).

`scaffold/fab.py` then writes `fab/`: Gerbers + Excellon zip, a JLC BOM and CPL (61 placed
parts; LCSC numbers live in `fab.py`, not in symbol fields, because `gen.py` regenerates
the schematics), an assembly PDF and `ORDERING.md`.

### Things found while finishing it (2026-09-24)

Like the regulator and the magnetometer cap above, several of these change a part:

1. **`J1` could not carry the current.** JST-GH is rated **1 A per contact** (LCSC's own
   listing says so) against `docs/14`'s **4.1 A** all-four-stalled case. Replaced, per Ben,
   by two 1.25 mm-drill wire pads for an **18 AWG XT30 pigtail**: the XT30 (15 A) lives on
   the wire, and the wire rather than the PCB takes the pack lead's pull and vibration.
2. **`C2` "100 µF/25 V" in 1210 does not exist** — 100 µF in 1210 stops at 10 V. Now
   **22 µF/25 V**, the same part as `C1`; at 8.4 V X5R keeps ~12 µF each, so ~25 µF of bulk
   on `VBATT`. If servo transients ever want more, that is a footprint change
   (a polymer tantalum), not a value change.
3. **The `RF` netclass was never in the project file.** `gen.py` defined it, but `gen.py`'s
   `.kicad_pro` template had Python `#` comments *inside the JSON string*, so it could not
   have written a valid file; the `.kicad_pro` on disk predated the RF change, and
   `GNSS_RF` was sitting in `Default` at 0.25 mm (59.9 Ω) the whole time this README said
   0.36. `gen.py` now builds the project JSON from Python tables (`NETCLASSES`,
   `BOARD_RULES`) and the file on disk has been merged to match.
4. **`Power` at 0.6 mm could not enter the fine-pitch pins.** A 0.6 mm track into a 0.3 mm
   LQFP/WSON/LGA pad on 0.5 mm pitch violates clearance to the neighbour. Now 0.3 mm
   (+3V3 is 112 mA, VIN ~60 mA; 0.3 mm is ~1 A on 1 oz), with 0.6/0.3 mm vias.
5. **The USB pair netclass was ~76 Ω, not 90.** 0.4/0.2 mm → **0.25/0.15 mm = 90.9 Ω**
   (`scripts/pcb_placement_report.py` prints both). At 12 Mbit/s over ~25 mm this is
   bookkeeping, not signal integrity.
6. **`J4`'s mouth was 1.1 mm inboard of the edge.** `gen_pcb.py` clamps every courtyard
   inside the outline, so the USB-C receptacle sat at *y* 140.25 with its face at 143.9 —
   a plug's overmold would have hit the PCB edge before seating. `J4` is now `EDGE_MOUNT`
   in `gen_pcb.py`, registered so its body front lands exactly on *y* = 145.0.
7. **Board rules now match JLCPCB's 4-layer capabilities** (via hole to track 0.2 mm,
   min track 0.15 mm because Freerouting necks 0.25 mm tracks to 0.187 at fine-pitch
   pads, silk text ≥ 1.0 mm). They were stricter in places JLC is not (hole clearance
   0.25) and looser where it is (text 0.8 mm).
8. **The power corner is frozen in `layout.py`'s `MANUAL_FIXUP`.** Changing *one* footprint
   (`J1`) reshuffled seven passives through `relax()`, and `finish.py`'s hand-drawn copper
   depends on that geometry. Pinned at the positions that passed DRC and the placement gate.
9. **Placement gate: 2 failures → 1.** Turning `R1` put its `VIN` pad beside `U1`; `C3`
   (3.40 mm vs 2.5) is the one left, accepted as before.

The antenna stays **passive** (`docs/14`) — routing is where "cheapest to make before
layout freezes" expired for the active-antenna option.

### IMU LDO, GNSS via fence, and simulation (2026-09-24, second pass)

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
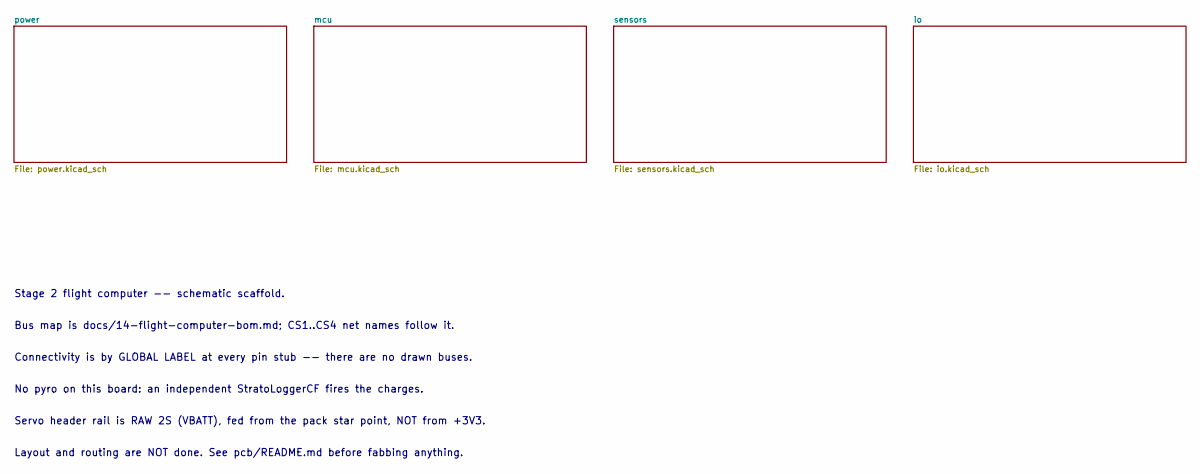
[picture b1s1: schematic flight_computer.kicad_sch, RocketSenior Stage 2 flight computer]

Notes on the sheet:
Stage 2 flight computer -- schematic scaffold.
Bus map is docs/14-flight-computer-bom.md; CS1..CS4 net names follow it.
Connectivity is by GLOBAL LABEL at every pin stub -- there are no drawn buses.
No pyro on this board: an independent StratoLoggerCF fires the charges.
Servo header rail is RAW 2S (VBATT), fed from the pack star point, NOT from +3V3.
Layout and routing are NOT done. See pcb/README.md before fabbing anything.

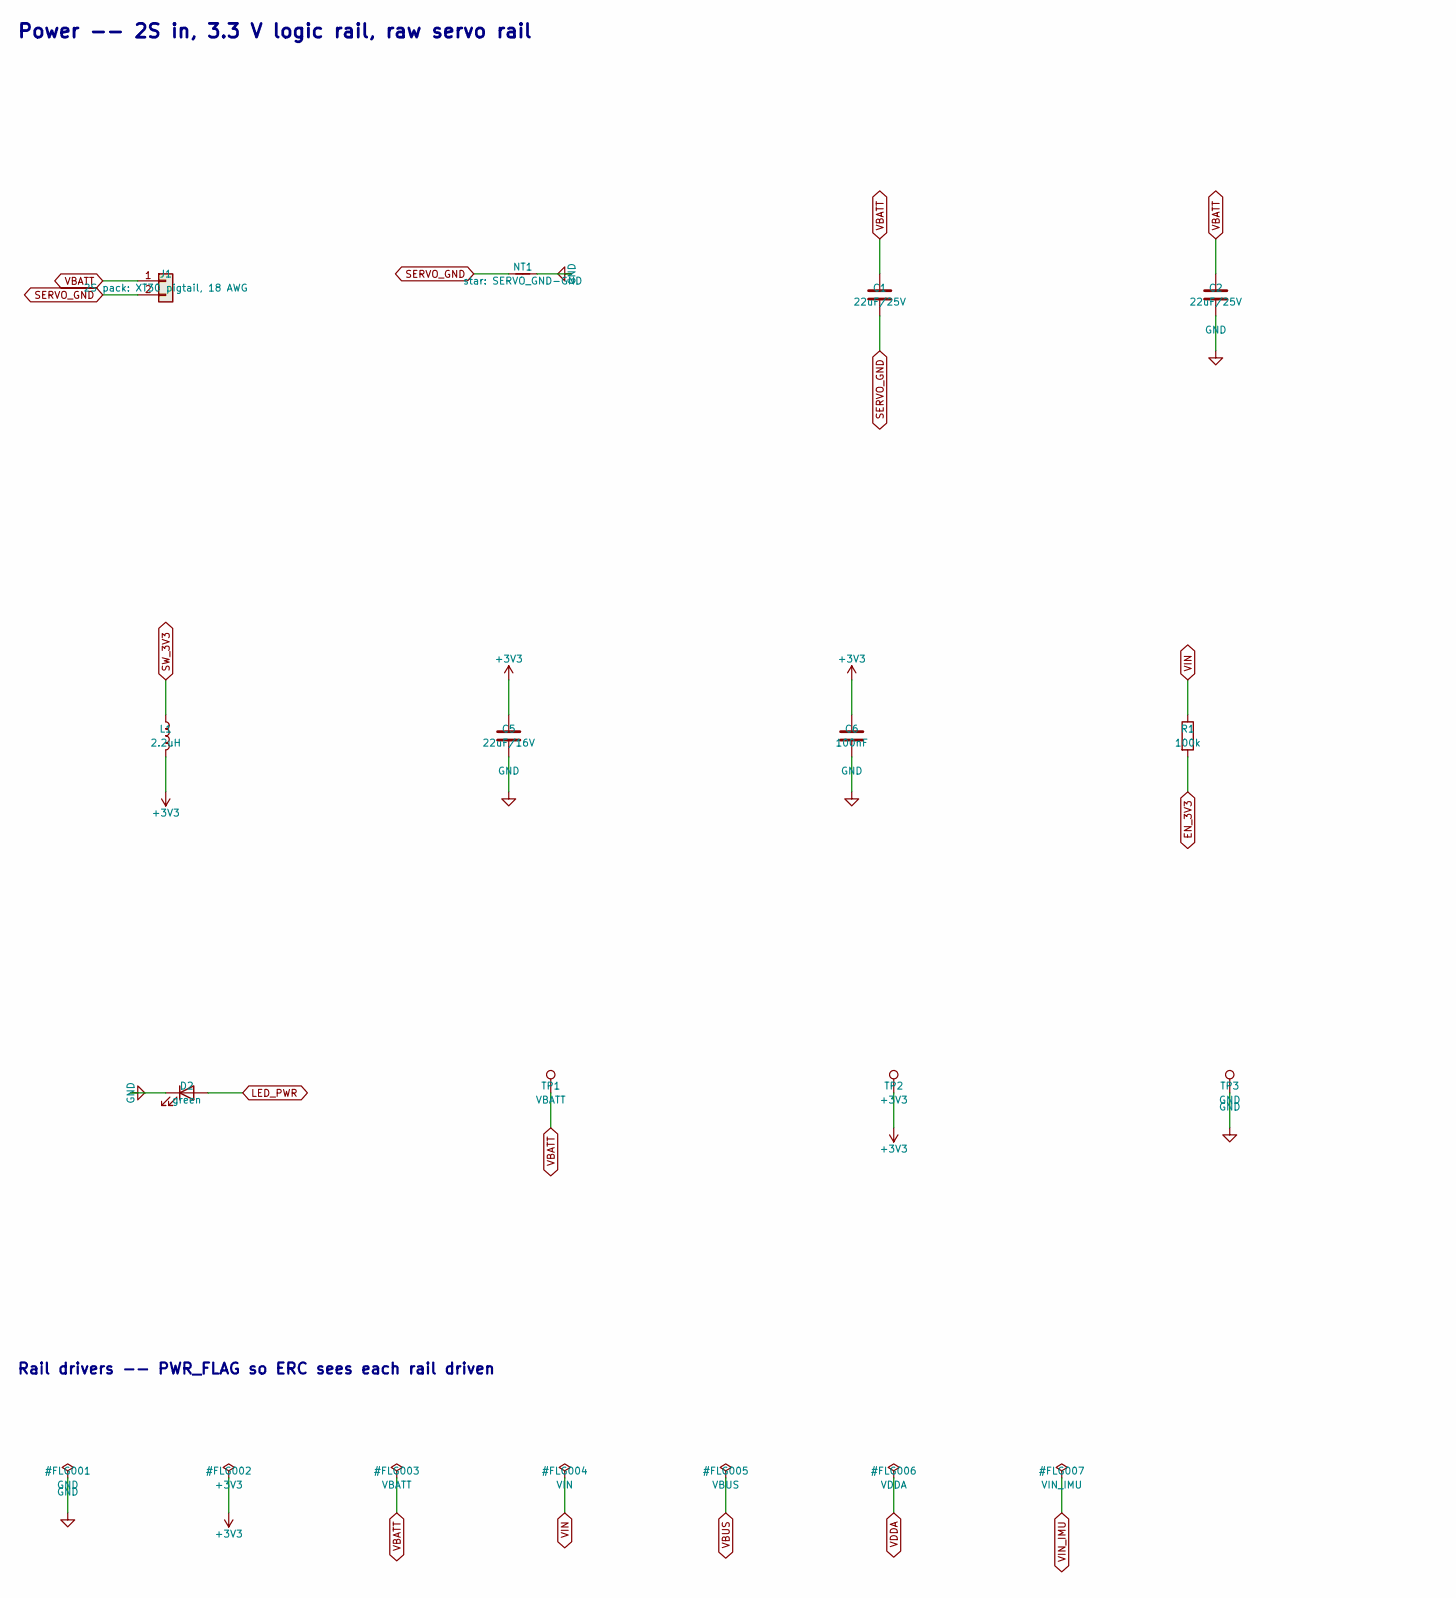
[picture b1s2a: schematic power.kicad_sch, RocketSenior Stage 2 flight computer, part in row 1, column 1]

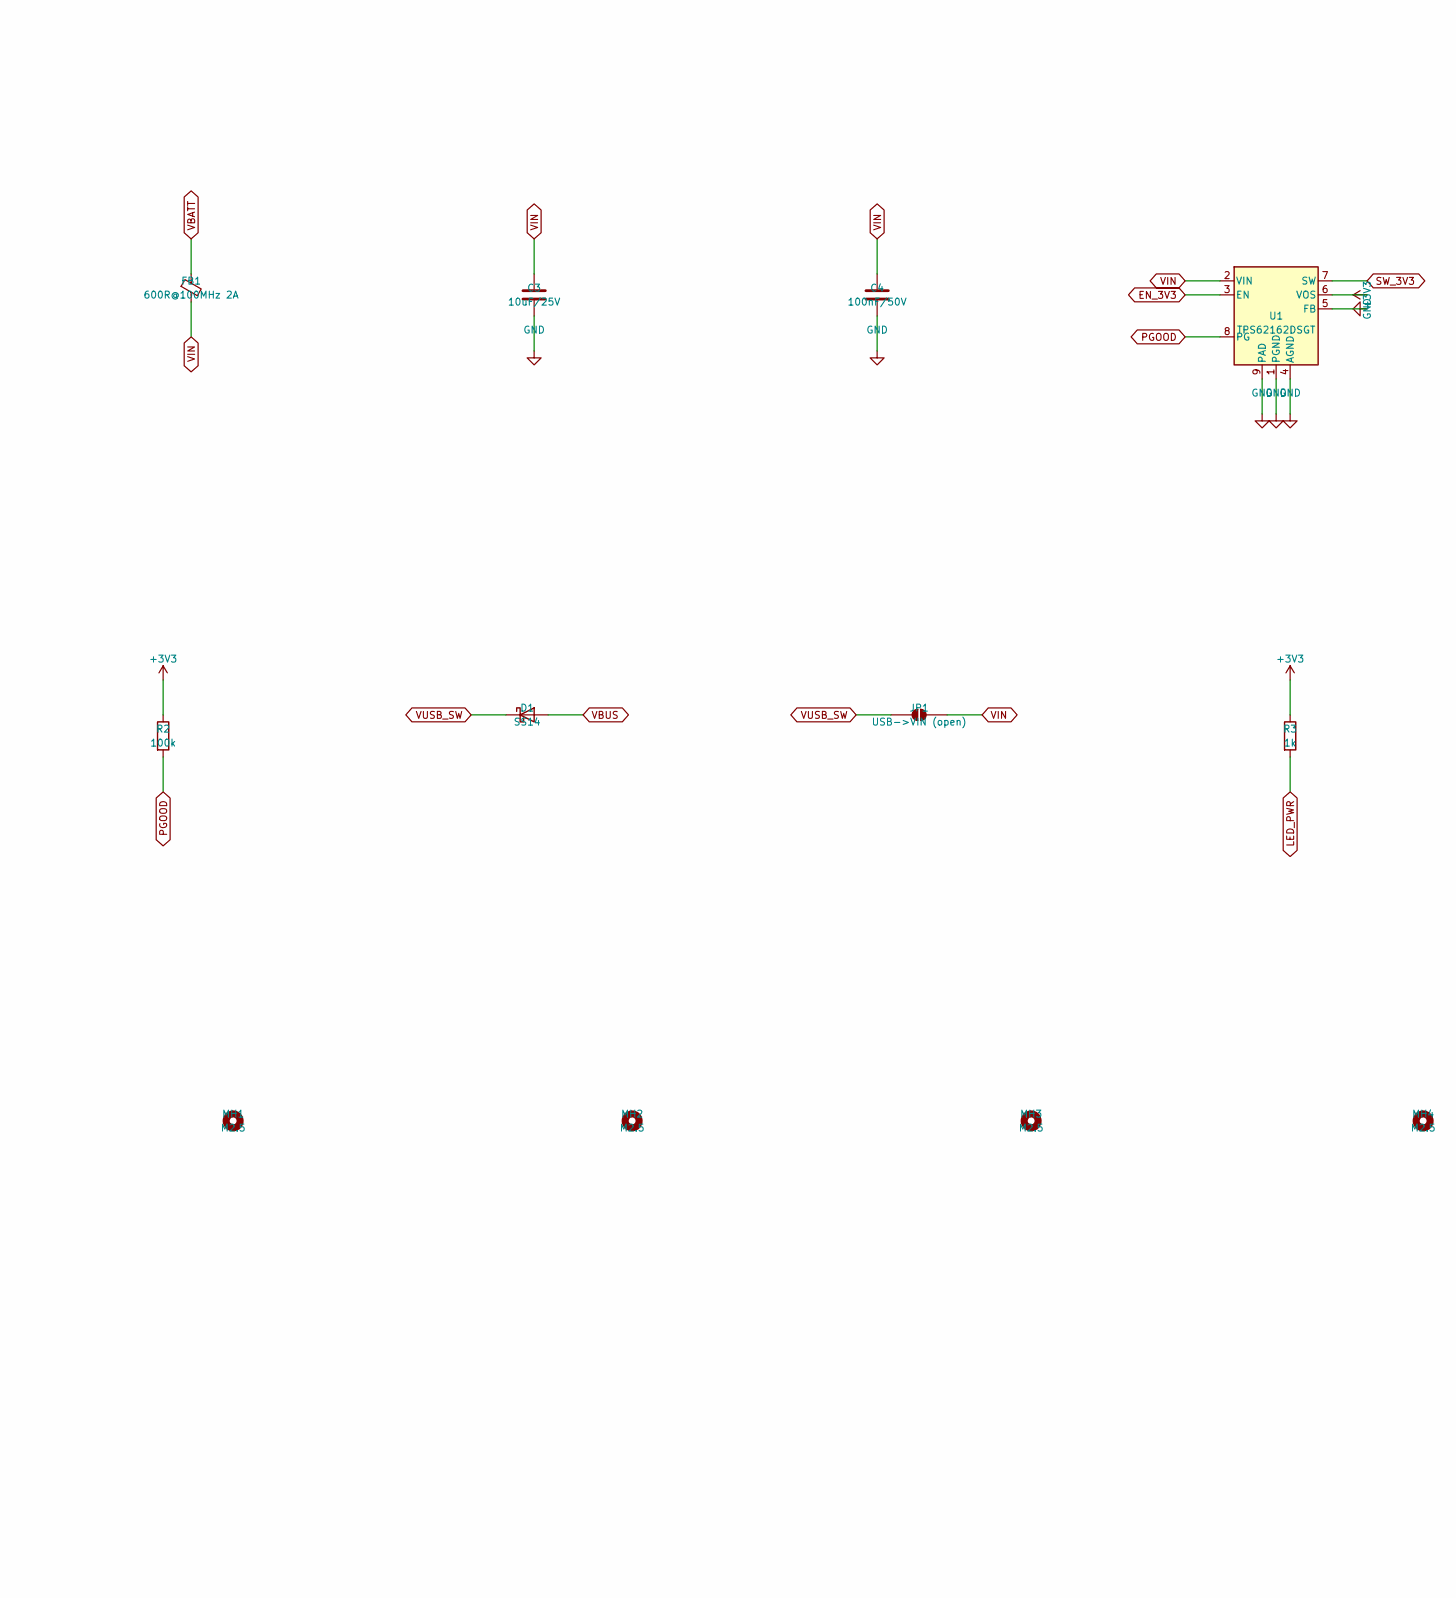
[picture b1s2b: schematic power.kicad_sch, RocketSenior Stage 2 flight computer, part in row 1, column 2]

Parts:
C1, C2: 22uF/25V; C_1210_3225Metric
C3: 10uF/25V; C_0805_2012Metric
C4: 100nF/50V; C_0402_1005Metric
C5: 22uF/16V; C_0805_2012Metric
C6: 100nF; C_0402_1005Metric
D1: SS14; D_SOD-123
D2: green; LED_0603_1608Metric
FB1: 600R@100MHz 2A; L_0805_2012Metric
J1: 2S pack: XT30 pigtail, 18 AWG; SolderWire-0.75sqmm_1x02_P4.8mm_D1.25mm_OD2.3mm
JP1: USB->VIN (open); SolderJumper-2_P1.3mm_Open_Pad1.0x1.5mm
L1: 2.2uH; L_1210_3225Metric
MH1, MH2, MH3, MH4: M2.5; MountingHole_2.7mm_M2.5
NT1: star: SERVO_GND-GND; NetTie-2_SMD_Pad0.5mm
R1, R2: 100k; R_0402_1005Metric
R3: 1k; R_0402_1005Metric
TP1: VBATT; TestPoint_Pad_D1.5mm
TP2: +3V3; TestPoint_Pad_D1.5mm
TP3: GND; TestPoint_Pad_D1.5mm
U1: TPS62162DSGT; Texas_DSG0008A_WSON-8-1EP_2x2mm_P0.5mm_EP0.9x1.6mm

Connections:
+3V3: C5.1, C6.1, L1.2, R2.1, R3.1, TP2.1, U1.6 (VOS); also elsewhere on the board
EN_3V3: R1.2, U1.3 (EN)
GND: C2.2, C3.2, C4.2, C5.2, C6.2, D2.1 (K), NT1.2, TP3.1, U1.1 (PGND), U1.4 (AGND), U1.5 (FB), U1.9 (PAD); also elsewhere on the board
LED_PWR: D2.2 (A), R3.2
PGOOD: R2.2, U1.8 (PG); also elsewhere on the board
SERVO_GND: C1.2, J1.2, NT1.1; also elsewhere on the board
SW_3V3: L1.1, U1.7 (SW)
VBATT: C1.1, C2.1, FB1.1, J1.1, TP1.1; also elsewhere on the board
VBUS: D1.2 (A); also elsewhere on the board
VIN: C3.1, C4.1, FB1.2, JP1.2 (B), R1.1, U1.2 (VIN); also elsewhere on the board
VUSB_SW: D1.1 (K), JP1.1 (A)

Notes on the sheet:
Power -- 2S in, 3.3 V logic rail, raw servo rail
Rail drivers -- PWR_FLAG so ERC sees each rail driven
